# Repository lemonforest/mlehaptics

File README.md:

# EMDR Bilateral Stimulation Device

**Version:** v0.7.x (Phase 7 Development)
**Last Updated:** 2025-12-23
**Status:** Phase 7 In Progress (P7.3 PWA Pattern Designer next) | P7.0-P7.2 Complete | Phase 6 Complete
**Project Phase:** Phase 7 (Patterns) | Phase 6 Complete | Phase 2 Complete (Time Sync) | Phase 1c Complete (Pairing)

**A dual-device EMDR therapy system with automatic pairing and coordinated bilateral stimulation**

> **Architecture Note:** This system uses a **hybrid BLE + ESP-NOW architecture**. BLE handles device discovery, pairing, and mobile app communication. ESP-NOW handles all peer-to-peer coordination with ±100μs timing precision. See [Connectionless Distributed Timing](docs/misc/Connectionless_Distributed_Timing_Prior_Art.md) for the foundational techniques.

Generated with assistance from **Claude Opus 4.5 (Anthropic)**

## 🤖 Development Methodology

This firmware was developed through guided AI iteration (Claude, Gemini, Grok), moving non-linearly between models and context windows. Cross-checking between sessions often surfaced insights that single-context iteration missed. The human role was direction, validation criteria, and "does this feel right" intuition—not code correction or complete domain expertise. AI contributed both implementation and domain research (protocol analysis, academic literature, patent landscape, algorithm selection).

What you see is what the AI produced through iterative guidance.

**Timing validation:** 240fps slow-motion capture on a consumer phone.

## 🎯 Project Overview

This project implements a two-device bilateral stimulation system for EMDR (Eye Movement Desensitization and Reprocessing) therapy. Two identical ESP32-C6 devices automatically discover and pair with each other, then provide synchronized alternating stimulation patterns with safety-critical non-overlapping timing. The system uses professional ERM (Eccentric Rotating Mass) motors for tactile stimulation with H-bridge bidirectional control, and includes a WS2812B RGB LED for dual-modality stimulation.

**Current Development Status:**
- ✅ Phase 0.4 JPL-compliant firmware complete (single-device testing)
- ✅ Phase 1c complete: Peer discovery with battery-based role assignment
- ✅ Phase 2 complete: NTP-style time synchronization (±30 μs over 90 minutes)
- ✅ Phase 6 complete: Bilateral motor coordination with PTP-inspired sync protocol
- ✅ GPIO remapping complete: H-bridge IN1 moved from GPIO20 to GPIO18 (eliminates crosstalk)
- ✅ Phase 7 P7.0-P7.2 complete: Pattern Engine, Scheduled Playback, Catalog Export (AD047)
- ⏳ Phase 7 next: P7.3 PWA Pattern Designer, P7.4 Legacy Mode Migration

**Key Features:**
- **Hybrid BLE + ESP-NOW**: BLE for discovery/pairing, ESP-NOW for sub-millisecond peer coordination
- **Configurable bilateral frequency**: 0.25-2 Hz (500-4000ms total cycle time)
- **Precise half-cycle allocation**: Each device gets exactly 50% of total cycle
- **Connectionless execution**: Devices sync once, then execute independently without coordination traffic
- **JPL-compliant timing**: All delays use FreeRTOS vTaskDelay() (no busy-wait loops)
- **Adaptive watchdog feeding**: Short cycles feed at end, long cycles feed mid-cycle + end (4-8x safety margin)
- **Open-source hardware**: Complete PCB designs, schematics, 3D-printable cases

### 🚀 Architecture Evolution (v0.7)

**v0.6 and earlier:** BLE maintained for peer-to-peer coordination throughout session. Time sync beacons sent via BLE GATT notifications. BLE connection required for bilateral motor coordination.

**v0.7 (Current):** **BLE Bootstrap Model** - BLE used only for initial discovery, pairing, and key exchange (~10 seconds). After bootstrap:
- Peer BLE connection **released** (frees radio for PWA)
- ESP-NOW handles all ongoing coordination (beacons, mode changes, shutdown)
- PWA can connect to SERVER device for real-time session control
- ±100μs timing precision (vs ±10-50ms with BLE)

This architectural shift improves timing precision by 100-500x and frees BLE radio resources for more responsive PWA communication.

## 🔌 Hardware Overview

### Physical Device

The device features a compact, ergonomic design with a 3D-printed enclosure housing a custom PCB based on the Seeed XIAO ESP32-C6 module.

<table>
<tr>
<td width="50%">

**Top View:** USB-C charging port, button, and status LED openings visible in the smooth enclosure surface.

</td>
<td width="50%">

**Bottom View:** Battery compartment access panel and mounting holes for internal components.

</td>
</tr>
</table>

**Size Reference:**

The device is significantly smaller than a standard computer mouse - approximately the length of an AA battery and comfortably fits in the palm of your hand. The compact form factor makes it ideal for discreet bilateral handheld therapy sessions.

### Key Hardware Components

- **MCU:** Seeed XIAO ESP32-C6 (RISC-V @ 160 MHz)
- **Motor:** ERM vibration motor with discrete MOSFET H-bridge control
- **LED:** WS2812B RGB LED for status feedback
- **Power:** Dual 320mAh LiPo batteries (640mAh total) with USB-C charging
- **Enclosure:** 3D-printed Nylon 12 SLS case (files in [hardware/enclosure/](hardware/enclosure/))
- **PCB:** Custom design (KiCad files in [hardware/pcb/](hardware/pcb/))

For complete hardware documentation, assembly instructions, and manufacturing files, see [hardware/README.md](hardware/README.md).

## 🛡️ Safety-Critical Development Standards

### ESP-IDF Framework Requirements
- **Mandatory Version**: ESP-IDF v5.5.0 (latest stable, enhanced ESP32-C6 support)
- **Platform**: PlatformIO espressif32 v6.12.0 with official Seeed XIAO ESP32-C6 support
- **Framework**: ESP-IDF (not Arduino) for real-time guarantees
- **Rationale**: Enhanced ULP support, BR/EDR + Wi-Fi coexistence, MQTT 5.0, proven stability

### JPL Institutional Coding Standard Compliance
This project follows **JPL Coding Standard for C Programming Language** for safety-critical medical device software:

**Memory Management:**
- ✅ No dynamic memory allocation (malloc/free) during runtime
- ✅ Static allocation only for all data structures
- ✅ Stack usage analysis with defined limits

**Control Flow:**
- ✅ No recursion - all algorithms use iterative approaches
- ✅ **No busy-wait loops** - all timing uses vTaskDelay() or hardware timers
- ✅ Limited function complexity (cyclomatic complexity ≤ 10)
- ✅ Single entry/exit points for all functions
- ✅ No goto statements except error cleanup

**Safety Requirements:**
- ✅ Comprehensive error checking for all function calls
- ✅ Bilateral timing precision ±10ms maximum deviation from configured cycle time
- ✅ Emergency shutdown within 50ms of button press
- ✅ Non-overlapping stimulation patterns (devices never stimulate simultaneously)
- ✅ 1ms dead time at end of each half-cycle (included within timing budget)

## ⚡ Quick Start

### Prerequisites
- **ESP-IDF v5.5.0**: Automatically managed by PlatformIO via `platformio.ini`
- **PlatformIO**: Install via VS Code extension or standalone
- **Two Seeed Xiao ESP32-C6 boards**: Hardware platform requirement (dual-device mode)
- **Hardware files**: See [hardware/README.md](hardware/README.md) for PCB manufacturing and case printing

### Build and Deploy

1. **Clone repository**:
   ```bash
   git clone https://github.com/lemonforest/mlehaptics.git
   cd mlehaptics
   ```

2. **Open in PlatformIO**: File → Open Folder → select project directory

3. **Verify ESP-IDF version configuration**: 
   - The `platformio.ini` file at the project root uses ESP-IDF v5.5.0
   - PlatformIO will automatically download and use the correct version
   - Build output will confirm "ESP-IDF v5.5.0" is being used
   
   **Working configuration in `platformio.ini`:**
   ```ini
   platform = espressif32 @ 6.12.0  ; Official Seeed XIAO ESP32-C6 support
   framework = espidf               ; Platform auto-selects ESP-IDF v5.5.0
   board = seeed_xiao_esp32c6       ; Official board definition
   ```

4. **Build project**: PlatformIO → Build (Ctrl+Alt+B)
   - First build will download ESP-IDF v5.5.0 (~1GB, takes ~10 minutes)
   - Verify build output shows "framework-espidf @ 3.50500.0 (5.5.0)"
   - Subsequent builds: ~1 minute incremental

5. **Upload to device(s)**: PlatformIO → Upload (Ctrl+Alt+U)

### First Power-On

**Single-Device Mode (Current Testing):**
1. **Power device** - use nRF Connect app to configure parameters
2. **5 operational modes**: Four presets + custom BLE-controlled mode
3. **Hold button 5 seconds** to shutdown

**Dual-Device Mode (Current Implementation):**
1. **Power both devices** - they will automatically pair within 30 seconds
2. **Status LED patterns**:
   - Fast blink = searching for server
   - Slow blink = waiting for client
   - Solid on = connected and bilateral active
3. **Test bilateral stimulation** - Motors alternate based on configured cycle time:
   - Default 1000ms cycle: Each motor active for 499ms (with 1ms dead time)
   - Fast 500ms cycle: Each motor active for 249ms (2 Hz bilateral rate)
   - Slow 2000ms cycle: Each motor active for 999ms (0.5 Hz bilateral rate)
   - **NO overlap** at any cycle time setting
4. **Hold button 5 seconds** on either device to shutdown both

## 🎬 Typical Bilateral Operation Flow

### Starting a Therapy Session

**Step 1: Power On Both Devices**
- Remove both devices from cases or turn on simultaneously
- Devices boot within 2-3 seconds
- Purple LED + status LED ON = waiting for peer

**Step 2: Automatic Pairing (< 10 seconds)**
- Both devices scan for Bilateral Control Service UUID
- Higher battery device initiates connection (becomes SERVER/MASTER)
- Lower battery device accepts connection (becomes CLIENT/SLAVE)
- **Pairing success**: 3× green synchronized flash on both devices
- **Pairing failure** (rare): 3× red flash, power cycle to retry

**Step 3: Session Starts Automatically**
- Default mode: 0.5Hz @ 25% duty (Mode 0)
- SERVER motors activate while CLIENT motors coast
- After 1 second: CLIENT motors activate while SERVER motors coast
- Bilateral alternation continues automatically
- **Session continuity**: If BLE briefly disconnects (<2 min), motors continue using frozen drift rate

**Step 4: Mode Switching During Session** (Optional)
- **Button tap** on either device: Cycle through modes (0→1→2→3→0...)
- Mode change propagates to peer device automatically
- Both devices synchronize to new frequency within 1 cycle
- Single quick blink confirms mode change
- **Available modes**: 0.5Hz, 1.0Hz, 1.5Hz, 2.0Hz @ 25% motor duty

**Step 5: Session Termination**
- **Normal end**: Session stops after configured duration (default 20 minutes)
- **Emergency shutdown**: 5-second button hold on **either** device
  - Purple LED ON during hold = release to shutdown
  - Both devices stop motors within 50ms
  - Both devices enter deep sleep simultaneously
- **Automatic shutdown**: Low battery warning → graceful stop

### Reconnection After Brief Disconnect

**If BLE connection drops during session:**
- ✅ **Motors continue** using frozen drift rate (CLIENT only)
- ✅ **Bilateral alternation maintained** (±2.4ms drift over 20 min)
- ✅ **Therapeutic continuity** preserved during BLE glitches
- ⏱️ **Safety timeout**: After 2 minutes, motors stop gracefully
- 🔄 **Reconnection**: Devices automatically reconnect, motors resume coordination

**Note:** Roles are preserved on reconnection (Phase 6n). If roles somehow swap, device logs warning (indicates bug).

## 🔧 Bilateral Timing Architecture

### Configurable Cycle Times

**Total cycle time** is the primary configuration parameter:
- **Range**: 500-4000ms (displayed to therapists as 0.25-2 Hz)
- **Default**: 1000ms (1 Hz, traditional EMDR bilateral rate)
- **Half-cycle allocation**: Each device gets exactly total_cycle / 2

### Timing Budget Examples

**1000ms Total Cycle (1 Hz):**
```
Server: [===499ms motor===][1ms dead][---499ms off---][1ms dead]
Client: [---499ms off---][1ms dead][===499ms motor===][1ms dead]
```

**500ms Total Cycle (2 Hz):**
```
Server: [===249ms motor===][1ms dead][---249ms off---][1ms dead]
Client: [---249ms off---][1ms dead][===249ms motor===][1ms dead]
```

**2000ms Total Cycle (0.5 Hz):**
```
Server: [===999ms motor===][1ms dead][---999ms off---][1ms dead]
Client: [---999ms off---][1ms dead][===999ms motor===][1ms dead]
```

### Dead Time Implementation

**1ms FreeRTOS delay at end of each half-cycle:**
- **JPL compliant**: Uses vTaskDelay(), no busy-wait loops
- **Watchdog feeding**: esp_task_wdt_reset() called during 1ms delay
- **Hardware protection**: GPIO write latency (~50ns) provides natural MOSFET dead time
- **Minimal overhead**: 1ms = 0.1-0.4% of half-cycle time
- **Included in budget**: Motor active time = (half_cycle_ms - 1)

## 📁 Project Structure

```
├── platformio.ini              # Build configuration (ESP-IDF v5.5.0)
├── README.md                   # This file
├── LICENSE                     # GPL v3 (software/firmware)
├── AI_GENERATED_DISCLAIMER.md  # Important safety notice
├── hardware/
│   ├── LICENSE                 # CERN-OHL-S v2 (hardware designs)
│   ├── README.md               # Hardware documentation
│   ├── pcb/                    # KiCad PCB project files
│   ├── enclosure/              # FreeCAD case designs
│   └── datasheets/             # Component specifications
├── docs/
│   ├── ai_context.md           # Complete rebuild instructions & API contracts
│   ├── requirements_spec.md    # Business requirements with dev standards
│   └── architecture_decisions.md # Technical rationale (PDR)
├── test/
│   ├── single_device_ble_gatt_test.c  # Phase 4 current implementation
│   └── *.md                    # Test-specific guides
├── include/
│   ├── config.h               # System constants, JPL compliance macros
│   ├── ble_manager.h          # BLE services and connection management
│   ├── led_controller.h       # PWM patterns and bilateral control
│   ├── nvs_manager.h          # Non-volatile storage interface
│   ├── button_handler.h       # ISR-based button timing
│   └── power_manager.h        # Deep sleep and session management
└── src/
    ├── main.c                 # FreeRTOS tasks and state machine (placeholder)
    └── ...                    # (actual code in test/ during development)
```

## 🎮 User Operation

### Normal Operation
- **Power on**: Devices auto-pair and start bilateral stimulation (dual-device mode)
- **Default session**: 20 minutes with automatic shutdown
- **Cycle time**: Configurable via mobile app (500-2000ms, displayed as Hz)
- **Status feedback**: Status LED shows connection and system state
- **Safety-critical timing**: Alternating half-cycles with NO overlap

### Button Controls
- **Button press**: Wake from deep sleep
- **1-2 second hold**: Re-enable BLE advertising for mobile app connection (SERVER role only)
- **5-second hold**: Emergency shutdown (both devices stop immediately)
- **15-second hold** (within 30s of boot): Factory reset (NVS clear)

### LED Status Indicators

| Status | Pattern | Description |
|--------|---------|-------------|
| 🔌 **BLE Connected** | 5× blink (100ms) | Mobile app or peer connected |
| 📡 **BLE Re-enabled** | 3× blink (100ms) | Advertising restarted (1-2s button hold) |
| 🪫 **Low Battery** | 3× blink (200ms) | Battery low warning |
| 🔧 **Factory Reset** | 3× blink (100ms) | NVS cleared successfully |
| 🎯 **Mode Change** | Single quick blink (50ms) | Mode switched |
| ⏸️ **Button Hold** | Continuous ON | Hold detected (1s+), waiting for action |
| ⏳ **Pairing Wait** | Solid ON + Purple LED | Waiting for peer (30s window) |
| 🔄 **Pairing Progress** | Pulsing 1Hz + Purple LED | Peer connection in progress |
| ✅ **Pairing Success** | 3× green synchronized | Peer paired successfully |
| ❌ **Pairing Failed** | 3× red synchronized | Peer pairing failed |

## 🔬 Development Configuration

### ⚠️ Critical Build System Constraint

**ESP-IDF uses CMake - PlatformIO's `build_src_filter` DOES NOT WORK!**

ESP-IDF framework delegates all compilation to CMake, which reads `src/CMakeLists.txt` directly. PlatformIO's `build_src_filter` option has **NO EFFECT** with ESP-IDF.

**Required approach**: Python pre-build scripts modify `src/CMakeLists.txt` for source file selection.

**📚 See for complete details:**
- **`docs/ESP_IDF_BUILD_CONSTRAINTS.md`** - Full explanation, examples, and common mistakes
- **`docs/architecture_decisions.md`** - AD022: Build System Architecture

### Build Standards and Quality Assurance

#### Code Quality Requirements
- **C language only**: No C++ features (JPL standard compliance)
- **No busy-wait loops**: All timing uses vTaskDelay() or hardware timers
- **Static analysis**: Code must pass JPL-compliant static analysis tools
- **Function complexity**: Maximum cyclomatic complexity of 10
- **Stack analysis**: All functions must have bounded stack usage
- **Error handling**: All functions return esp_err_t for operations that can fail

#### Build Flags (config.h)
```c
// Development mode configuration
#define ENABLE_FACTORY_RESET    1   // 0 = disable for production
#define TESTING_MODE           1   // 0 = production build
#define DEBUG_LEVEL            3   // 0 = no logging, 4 = full debug

// JPL Coding Standard compliance
#define JPL_COMPLIANT_BUILD    1   // Enable JPL standard checks
#define ESP_IDF_TARGET_VERSION "v5.5.0"  // Verified ESP-IDF version

// Bilateral timing configuration
#define BILATERAL_CYCLE_TOTAL_MIN_MS    500     // 2 Hz max
#define BILATERAL_CYCLE_TOTAL_MAX_MS    2000    // 0.5 Hz min
#define BILATERAL_CYCLE_TOTAL_DEFAULT   1000    // 1 Hz default
#define MOTOR_DEAD_TIME_MS              1       // FreeRTOS delay
```

#### Validation Requirements
- **Unit testing**: Minimum 90% code coverage for safety-critical functions
- **Integration testing**: Full two-device bilateral coordination validation at multiple cycle times
- **Timing precision**: Automated testing of ±10ms bilateral timing requirements
- **JPL compliance**: Static analysis verification of coding standard adherence
- **ESP-IDF compatibility**: Build verified against v5.5.0 (October 20, 2025)

### Testing Protocol

#### Bilateral Coordination Testing
1. Power both devices simultaneously
2. Verify automatic pairing within 30 seconds
3. Test at multiple cycle times (500ms, 1000ms, 2000ms)
4. Confirm non-overlapping stimulation patterns with oscilloscope
5. Test coordinated shutdown from either device

#### Single-Device Testing  
1. Power single device
2. Use nRF Connect app for BLE configuration
3. Test all 5 operational modes
4. Test button wake/shutdown functionality

#### Timing Validation
1. **Oscilloscope verification**: Measure actual bilateral timing precision at all cycle times
2. **Stress testing**: 24-hour continuous operation validation
3. **Emergency response**: Verify <50ms shutdown response time
4. **Connection loss**: Test graceful degradation when devices disconnect
5. **Watchdog testing**: Verify TWDT feeding during 1ms dead time periods

## ⚠️ Important Safety Notice

**This code was generated with AI assistance and implements safety-critical medical device functionality. Please read `AI_GENERATED_DISCLAIMER.md` for critical safety information before use.**

### Required Validation for Medical Use
- **Complete code review** by qualified embedded systems engineer
- **JPL coding standard verification** using certified static analysis tools
- **ESP-IDF v5.5.0 compatibility** verified on target hardware (October 20, 2025)
- **Safety validation** for therapeutic applications following IEC 62304
- **Timing precision validation** with laboratory-grade measurement equipment
- **EMC compliance testing** for medical device environments
- **Battery safety validation** for portable medical equipment

### Development Environment Requirements
- **ESP-IDF v5.5.0**: Required version for enhanced ESP32-C6 support and BLE stability
- **Static analysis tools**: PC-Lint, Coverity, or equivalent for JPL compliance
- **Timing measurement**: Oscilloscope or logic analyzer for bilateral precision testing
- **Multi-device testing**: Minimum two ESP32-C6 boards for integration testing

## 📚 Documentation

### Web App
- **[MLE Haptics PWA](https://lemonforest.github.io/mlehaptics-pwa/)**: Web Bluetooth control app for device configuration and monitoring

### Clinical Research & Evidence Base

This device operates within evidence-based EMDR bilateral stimulation parameters. We've compiled comprehensive research documentation to inform both clinical use and device development:

- **[EMDR Bilateral Stimulation: Evidence-Based Parameters](docs/EMDR_bilateral_stimulation_Evidence-based_parameters_for_clinical_practice.md)**: Comprehensive review of EMDRIA guidelines, frequency ranges (0.5–2 Hz standard), modality comparisons (eye movements d=0.41–0.91), brainwave entrainment research, emerging applications, contraindications, and commercial device specifications. Includes phone-sized quick reference and poster-sized infographic datasets.

- **[The Slow Frequency Research Frontier](docs/EMDR_Slow_BLS_Research_Frontier.md)**: Addendum exploring sub-0.5 Hz bilateral stimulation—an undefined research gap. Documents theoretical rationale for slow BLS including cardiac coherence alignment (0.1 Hz), breathing synchronization (0.25 Hz), and infraslow brain oscillations. Proposes frequency taxonomy: Standard (0.5–2 Hz), Deep Resourcing (0.25–0.5 Hz), Cardiac Coherence (0.08–0.12 Hz), and Infraslow Exploration (0.01–0.08 Hz).

### Research & Prior Art

This project developed foundational techniques for **connectionless distributed timing**—a class of systems that achieve synchronized actuation across wireless nodes *without* real-time coordination traffic during operation. While we built an EMDR device, the architecture enables countless applications from emergency vehicle light bars to drone swarms.

- **[Connectionless Distributed Timing: A Prior Art Publication](docs/misc/Connectionless_Distributed_Timing_Prior_Art.md)**: Defensive publication establishing open-source prior art for synchronized wireless actuation. Documents the journey from BLE stack timing jitter to recognizing the constraint was artificial. Validated with SAE J845 Quad Flash at 240fps (zero-frame overlap). Published to ensure these techniques remain freely available.

- **[Distributed Sensing: A Project Lab Manual](docs/misc/Distributed_Sensing_Lab_Manual.md)**: Educational guide for students, hobbyists, and researchers exploring distributed sensing with synchronized wireless nodes. Covers acoustic beamforming, wind mapping, infrasound detection, mmWave radar for building occupancy/safety, and emergency response applications. Scales from weekend science project to operational systems.

- **[Chess as a Spectral Lattice Fermion System](docs/chess-maths/chess_spectral_research_notebook.md)**: Primary research notebook treating the chess board as a classical lattice fermion system. Documents a rank-5 total fiber bundle (3 off-diagonal symmetric, 1 antisymmetric for pawn directionality, 1 diagonal rook shadow), a 5-tuple spectral quantum-number classification of all six pieces, an exact capture decomposition into movement + annihilation + cross-term, and a 640-dim HDC encoding (D4 irreps × fiber channels × eigenmodes) that ties into UTLP S3. Pawn is analyzed as a non-Hermitian chiral fermion; piece values are spectrally derived from movement-graph topology (r ≈ 0.97 with traditional values, no king domination). Explicit about the Level 2 / Level 3 boundary — the model captures structural and thermodynamic properties of the game but provably cannot generate legal moves or tactical sequences, and deliberately does not equate any of this with chess *strategy*.

- **[Chess Spectral Lattice Fermion Viewer](https://lemonforest.github.io/chess-maths-the-movie/)**:  In-browser spectral-analysis instrument for chess corpora produced by the chess-spectral encoder.

- **[4D Chess Spectral — v1 Validation Notebook](docs/chess-maths/chess_spectral_4d_notebook.md)**: Companion validation notebook for the 4D extension of the chess-spectral encoder (40,960-dim on Z₈⁴, up from 640-dim on Z₈²). Records which parts transferred cleanly from 2D (Kronecker-sum eigenbasis, Oana & Chiru piece-mobility counts, fiber algebra including `A_queen = A_rook + A_bishop`) and what changed (bishop parity partition at 4D, pawn antisymmetric fiber block-diagonal along the w-axis). Reframes the previously-conflated "rank-3" cross-piece finding into two distinct claims: a basis-free edge-support orthogonality (Claim 1) and a representation-specific grid-spectral rank-3 in the tensor-DCT basis (Claim 2) — with the "intrinsic geometry" phrasing from earlier drafts explicitly retracted. Surfaces that the named piece vocabulary under-specifies the 4D geometric primitives by exactly two classes — a trihedral (HD = 3) and tetrahedral (HD = 4) stepper — since "king = one-step bishop + one-step rook" only exhausts Chebyshev-1 in 2D.

- **[python-chess4d-oana-chiru](https://github.com/lemonforest/python-chess4d-oana-chiru)**: Python implementation of O&C 4D Chess. https://doi.org/10.3390/appliedmath6030048

- **[LOGO HDC — Research Notebook](docs/chess-maths/logo_research_notebook.md)**: Pattern-validation spike testing whether the split-object-with-fiber-matrix construction from the chess-spectral work generalizes to a non-chess domain. Uses a research subset of LOGO (turtle graphics) as a fully-enumerable test case — 12 command atoms, ~20 grammar productions, rasterized canvas as geometry. Confirms F₁ (vocab × syntax) and F₂ (syntax × geometry) factorizations recover interpretable structure, including D4 symmetry modes in the subdominant F₂ spectrum, and that fibers act as transport maps for structural deltas. L7b finds partial-trace fibers drift with the trace but do *not* extrapolate forward, reshaping the trajectory hypothesis before the chess instantiation. Iterative, with an honest retraction of the iteration-1 reversibility-via-binding claim.

#### The Metric Field and Its Primitives — Companion Textbook

- **[The Metric Field and Its Primitives (PDF)](docs/srmech/metric-field-and-its-primitives.pdf)** — companion textbook to the [srmech](https://pypi.org/project/srmech/) package and the [MFO research notebook](docs/antikythera-maths/mfo_spectral_research_notebook.md). Consolidates the substrate-vs-excitation ontology, the 14-class primitive vocabulary at substrate level, and the cascade-composition discipline that `srmech` implements computationally. Reader-facing entry point for the foundational-ontology layer of the spectral-research collection.

  Also available on [ReadTheDocs](https://mlehaptics.readthedocs.io/srmech/metric-field-and-its-primitives.pdf) (static asset alongside the notebooks).

#### Spectral Research Cluster — the Rosetta Stone

The chess-spectral notebook is the *methodological anchor* of a five-sibling research cluster. Each sibling ports the same algebraic substrate — **finite cyclic groups + graph-Laplacian eigenbasis + the BIP integer-ALU encoder pattern** — to a different evidentiary object. The cluster is intentionally *not* consolidated into a single paper because the evidentiary objects differ; what binds them is the substrate, and each successful port is empirical evidence that the substrate generalises beyond its origin domain.

| Sibling | Evidentiary object | Notebook | Status |
| :--- | :--- | :--- | :--- |
| chess-maths | Chess board / piece moves | [chess_spectral_research_notebook.md](docs/chess-maths/chess_spectral_research_notebook.md) | **Methodological anchor** — Rank-5 fiber bundle, 5-tuple piece classification, the §42 cross-disciplinary methodology note that the rest of the cluster is built around. |
| othello-maths | Othello disc-flipping | [othello_spectral_research_notebook.md](docs/othello-maths/othello_spectral_research_notebook.md) | **§10.7 ray-flanking** — sheaf-Laplacian raycast that the doom-spectral Track 3 reuses verbatim. |
| antikythera-maths (Antikythera) | Hellenistic bronze (~150–60 BCE) | [antikythera_spectral_research_notebook.md](docs/antikythera-maths/antikythera_spectral_research_notebook.md) | Cyclic-group ratios + Laplacian eigenbasis read off the gear DAG; established the integer-ALU + cosine-LUT + Q-format discipline the other siblings reuse. |
| antikythera-maths (Ephemerides) | JPL DE441 live ephemeris (38 bodies) | [ephemerides_spectral_research_notebook.md](docs/antikythera-maths/ephemerides_spectral_research_notebook.md) | **Shipped to PyPI** as [`ephemerides-spectral`](https://pypi.org/project/ephemerides-spectral/) — `Z_{2^32}` BIP encoder, Phase-9 adaptive couplings, full Sol Symphony Times + Sol Moon Times for every body in BODIES, all ten JPL Power-of-Ten rules satisfied. |
| antikythera-maths (DOOM) | id Tech 1 / linuxdoom-1.10 source tree | [doom_spectral_research_notebook.md](docs/antikythera-maths/doom_spectral_research_notebook.md) | **End-to-end existence proof — the capstone.** See below. |
| chess-maths (LOGO) | Turtle-graphics grammar (research subset) | [logo_research_notebook.md](docs/chess-maths/logo_research_notebook.md) | Pattern-validation spike confirming F₁/F₂ factorization generalises beyond chess. |

##### doom-spectral as the capstone

The other siblings each port the spectral substrate to a *greenfield* problem: they own the codebase end-to-end, so the substrate never has to coexist with anyone else's design. **doom-spectral is the first instance where the full spectral pipeline is wired into a *legacy* engine that's already running**, with its own subsystem boundaries (renderer, BSP, sector specials, demo loop, cheat machinery, X11 video path) — and where the spectral substitution must coexist with all of them without breaking the original game.

The fix branch (PR #221, `fix/doom-spectral-integration-build`) took linuxdoom-1.10 from "won't compile" to "runnable engine with visible spectral lighting effects driven by Track-4 graph diffusion behind a 1993-vintage cheat code." Two new sections in the doom-spectral notebook document the result:

- **[§6 — Live Integration into linuxdoom-1.10](docs/antikythera-maths/doom_spectral_research_notebook.md#6-live-integration-into-linuxdoom-110-may-2026)** — verbose walk-through of every hook landed in the engine. Written so a reader doesn't need linuxdoom's source open: the seven-step arc from "doesn't compile" to "runnable engine with IDSPECTRAL pulse," the module-boundary discipline, the **TrueColor translation layer** (8-bit indexed renderer → 32-bit XImage via 256-entry uint32 LUT, pure ALU, generalises to any 1990s 8-bit engine landing on a modern X server), the map registration gate, the **BIP→lightlevel data flow per tic**, the SCRAMBLE-encoded `IDSPECTRAL` cheat sequence, and verified live behaviour against the shareware doom1.wad.
- **[§7 — Replacing FPU Engine Bits with Graph-Laplacian Primitives](docs/antikythera-maths/doom_spectral_research_notebook.md#7-replacing-fpu-engine-bits-with-graph-laplacian-primitives--a-generic-procedure)** — generalised 8-step procedure for porting *any* FPU-leaning engine subsystem (collision, lighting, AI, audio diffusion) to the spectral / ALU substrate, with side-by-side doom-spectral and chess-spectral instantiations of each step. Includes the wins (cosine similarity vs Euclidean distance; graph diffusion vs raycast accumulation; anchors decouple geometry from semantics) and the **honest limits** (sub-cell precision, dynamic geometry, one-shot events). Closes with the capstone framing: the §7.1 procedure is now exportable to other legacy engines (Quake, Wolfenstein 3D, Duke3D, ROTT — all candidates for the same treatment).

The successful integration — visible IDSPECTRAL pulse on E1M1, demos play through a version mismatch via a PCB-style jumper, the secret-sector hum **bleeds one hop along the spectral adjacency graph** into corridors the player can actually see (a truncated form of Track 4 heat diffusion) — is the strongest available evidence that the §7.1 procedure generalises beyond greenfield problems. The Rosetta Stone arc has its anchor points: chess-spectral §42 at the methodological end, doom-spectral §6 + §7 at the empirical end.

### Consciousness & Therapeutic Mechanisms

- **[The Simulation-Lucid Phenotype](docs/misc/simulation_lucid_phenotype.md)**: Proposes complete aphantasia (~1% of population) as a natural experiment for consciousness research. Argues that removing the cortical imagery "rendering engine" reveals the interoceptive-somatic substrate underlying all cognition. Synthesizes aphantasia neuroscience, predictive processing, Craig's interoceptive hierarchy, Damasio's somatic markers, and psychedelic pharmacology (REBUS model) to predict that therapeutic benefit operates at substrate level, not the visual overlay. Includes implications for trauma therapy, meditation science, animal cognition, and IQ measurement.

- **[What Removing the Overlay Reveals](docs/misc/simulation_lucid_phenotype_companion_piece.md)**: Accessible companion to the simulation-lucid phenotype paper. Frames the core insight — that body-based processing is where the deepest therapeutic and contemplative work happens, for everyone — with practical consequences for psychedelic trials (stratifying outcomes by imagery ability), trauma therapy (guided interoception as alternative to imagery-based approaches), and the 2,500-year precedent of body-based contemplative practice. Includes first-principles account of mystical experience grounded in insular cortex neuroanatomy.

- **[Proprioceptive Spatial Construction](docs/misc/proprioceptive_spatial_construction.md)**: Identifies a taxonomic gap in cognitive science — using the body's position-sensing system as a generative spatial reasoning instrument to construct manipulable models of external objects without visual imagery or prior tactile experience. Synthesizes evidence from aphantasia research, blindness studies, embodied cognition, and multisensory neuroscience showing parietal cortex operates as a supramodal spatial hub accepting proprioceptive input interchangeably with vision.

### AI Collaboration & Methodology

- **[Integrative Capacity as a Trackable Metric](docs/misc/Integrative_Capacity_AI_Synthesis_Alignment.md)**: Meta-observation on AI alignment—proposes **Semantic Tension Span (STS)** as a metric for measuring AI synthesis vs retrieval. Uses the mlehaptics corpus (this project) as a labeled dataset of verified cross-domain isomorphisms: immunology→firmware, geophysics→packet radio, thermodynamics→governance. Argues that RLHF suppresses high-tension bridges as "hallucination" when they should be validated by functional stability (does the code compile? does the state machine execute?).

### Technical Reports
- **[Bilateral Time Sync Protocol Technical Report](docs/Bilateral_Time_Sync_Protocol_Technical_Report.md)**: Comprehensive documentation of the PTP-inspired BLE synchronization protocol achieving +/-30us over 90 minutes

### Protocol Specifications (UTLP/RFIP)
- **[UTLP Specification](docs/misc/UTLP_Specification.md)**: Universal Time Lord Protocol - peer-to-peer time synchronization for embedded swarms
- **[UTLP Technical Report v2](docs/archive/UTLP_Technical_Report_v2.md)**: Detailed protocol analysis with stratum hierarchy and passive opportunistic adoption
- **[UTLP Technical Supplement S1](docs/misc/UTLP_Technical_Supplement_S1.md)**: Extended theory - Seismic chirp beacons, dynamic macroscopic lattice, audio sync, and sensor fusion applications
- **[UTLP Technical Supplement S2](docs/misc/UTLP_Technical_Supplement_S2.md)**: Biological Governance - Immune system architecture for distributed time synchronization (fault isolation via statistical filtering, endosymbiotic integration, speciation via encryption)
- **[UTLP Technical Supplement S3](docs/misc/UTLP_Technical_Supplement_S3.md)**: Vector Time - Hyperdimensional coprime cyclic representation replacing scalar counters with phase chords (Chinese Remainder Theorem, KalmanHD, similarity-based sync)
- **[UTLP Technical Supplement S4](docs/misc/UTLP_Technical_Supplement_S4.md)**: Partition Handling - CRT aliasing horizon as partition detection mechanism in coprime cyclic time systems
- **[HDC Objects as Musical Instruments](docs/misc/hdc_as_instruments.md)**: Source-filter model from acoustics applied to hyperdimensional computing — designing base vectors with deliberate spectral envelopes (formants, Walsh-Hadamard partitioning) instead of random projections. Connects orchestration theory, CDMA telecommunications, and Sethares' timbre-scale duality to HDC vector design.
- **[Spectral Convergence Conjecture](docs/misc/Spectral_Convergence_Conjecture.md)**: Precisely stated conjecture with proof sketch — for any finite-dimensional representation system with group symmetry, the optimal basis converges to irreducible representations (Peter-Weyl → Bochner → Karhunen-Loeve). Explains why six independent fields (neural nets, transformers, HDC, CDMA, approximation theory, grid cells) all converged on spectral structure over randomness.
- **[UTLP Executive Summary](docs/misc/UTLP_Executive_Summary.md)**: Hardware engineer's build guide - critical numbers, beacon format, genesis election rules, and essential code patterns for implementing UTLP from scratch
- **[RFIP Addendum](docs/misc/UTLP_Addendum_Reference_Frame_Independent_Positioning.md)**: Reference-Frame Independent Positioning - spatial awareness without external reference frames
- **[RFIP Technical Specification](docs/misc/RFIP_Technical_Specification.md)**: Spatial Loom implementation - HAL architecture, data hierarchy (RSSI → CSI → TDoA → FTM → UWB), silicon detection
- **[802.11mc FTM Reconnaissance](docs/802.11mc_FTM_Reconnaissance_Report.md)**: Fine Time Measurement research for ±1-2m ranging capability

### For Builders
- **[hardware/README.md](hardware/README.md)**: PCB manufacturing, case printing, assembly instructions
- **[test/SINGLE_DEVICE_BLE_GATT_TEST_GUIDE.md](test/SINGLE_DEVICE_BLE_GATT_TEST_GUIDE.md)**: BLE GATT testing with nRF Connect

### For Developers
- **[docs/ai_context.md](docs/ai_context.md)**: Complete API contracts and rebuild instructions with JPL compliance
- **[docs/adr/README.md](docs/adr/README.md)**: Architecture Decision Records (48 ADRs documenting design rationale)
- **[docs/KNOWN_ISSUES.md](docs/KNOWN_ISSUES.md)**: Known bugs and limitations being tracked for resolution
- **[docs/requirements_spec.md](docs/requirements_spec.md)**: Business requirements with development standards
- **[CLAUDE.md](CLAUDE.md)**: Developer reference for AI-assisted workflow
- **Doxygen docs**: Run `doxygen Doxyfile` for comprehensive API documentation

### For Users
- **This README**: Setup and operation instructions with safety requirements
- **AI_GENERATED_DISCLAIMER.md**: Critical safety validation requirements

## 🤝 Contributing

See [CONTRIBUTING.md](CONTRIBUTING.md) for contribution guidelines.

**In brief:** This is a personal research project. Bug reports and suggestions via GitHub issues are welcome! I prefer to implement changes myself to ensure hands-on hardware testing and consistency with the AI-assisted development workflow. Forks are encouraged if you want to take the project in your own direction.

### Code Standards Reference

If you're forking or studying the code, these are the standards followed:

- **C language**: Strictly C (no C++ features)
- **JPL coding standard**: All safety-critical rules must be followed
- **No busy-wait loops**: All delays use vTaskDelay() or hardware timers
- **Doxygen-style comments**: Required for all public functions
- **ESP-IDF v5.5.x conventions**: Follow latest framework best practices
- **Hierarchical error handling**: Proper esp_err_t propagation

## 📄 License

This project uses **dual licensing** to separate software and hardware:

### Software License: GPL v3

All firmware, software, and code in this repository is licensed under the **GNU General Public License v3.0**.

- **Applies to:** All `.c`, `.h`, Python scripts, and other software files
- **Location:** [LICENSE](LICENSE)
- **Summary:** Copyleft license - modifications must be shared under same license
- **Compatibility:** Can be integrated into GPL-compatible projects

### Hardware License: CERN-OHL-S v2

All hardware designs (PCB schematics, layouts, enclosures) are licensed under the **CERN Open Hardware License Version 2 - Strongly Reciprocal**.

- **Applies to:** KiCad files, gerbers, FreeCAD models, STL/STEP files in `/hardware`
- **Location:** [hardware/LICENSE](hardware/LICENSE)
- **Summary:** Copyleft for hardware - derivative designs must be shared under same license
- **Compatibility:** Reciprocal like GPL but for physical designs

### Why Dual Licensing?

- **Software copyleft (GPL v3):** Ensures firmware improvements benefit the community
- **Hardware copyleft (CERN-OHL-S v2):** Ensures PCB/case improvements benefit the community
- **Strong reciprocal:** Both licenses require sharing modifications under the same terms
- **Patent protection:** Both provide protection against patent claims
- **Medical device safety:** Copyleft ensures safety improvements are shared publicly

### Attribution Requirements

When using or modifying this project:
- **Retain all license notices** in source files and documentation
- **Document modifications** with dates and descriptions
- **Share modified source** if distributing devices or derivatives
- **Credit original project:** Link to this repository

## 📄 Attribution

- **License:** Dual - [GPL v3](LICENSE) (software) + [CERN-OHL-S v2](hardware/LICENSE) (hardware)
- **AI Assistant**: Claude Sonnet 4 (Anthropic) - Code generation assistance
- **Development Standards**: JPL Institutional Coding Standard for C Programming Language
- **Framework**: ESP-IDF v5.5.0 (Espressif Systems) - Verified October 20, 2025
- **Human Engineering**: Requirements specification, safety validation, hardware design
- **Project**: MLE Haptics - mlehaptics.org
- **Generated**: 2025-09-18, Updated: 2025-12-23

Please maintain attribution when using or modifying this code or hardware designs.

## 🔗 Related Projects and Future Development

### Phase 0.4: Single-Device Testing & Hardware Validation (Complete)
- **Phase 0.4 firmware**: JPL-compliant single-device operation with BLE GATT control
- **5 operational modes**: Four presets + custom BLE-configured mode
- **Hardware v0.663399ADS**: GPIO crosstalk fixes implemented, ready for production
- **Mobile app integration**: BLE GATT Configuration via nRF Connect

### Phase 1b/1c: Dual-Device Peer Discovery and Role Assignment (Complete)
- ✅ **Phase 1b Complete**: Peer discovery with UUID switching (Bilateral UUID 0-30s, Config UUID 30s+)
- ✅ **Phase 1b.1 Complete**: Multiple connection support (peer + mobile app simultaneously)
- ✅ **Phase 1b.2 Complete**: Role-aware advertising (SERVER continues, CLIENT stops)
- ✅ **Phase 1b.3 Complete**: Exclusive pairing (once bonded, only that peer can connect until NVS erase)
- ✅ **Phase 1c Complete**: Battery-based role assignment via BLE Service Data (higher battery initiates as SERVER)

### Phase 2: NTP-Style Time Synchronization (Complete)
- ✅ **Time Sync Protocol**: NTP-style beacon exchange via ESP-NOW achieving ±30 μs over 90 minutes
- ✅ **Dual-Clock Architecture**: System clock untouched, synchronized time via API
- ✅ **Quality Metrics**: 0-100% sync quality with automatic recovery from anomalies
- ✅ **90-Minute Stress Test**: 271 ESP-NOW beacons exchanged, 95% quality sustained

### Phase 6: Bilateral Motor Coordination (Complete)
- ✅ **ESP-NOW Coordination**: Sub-millisecond peer sync (±100μs jitter vs BLE's ±10-50ms)
- ✅ **PTP-Inspired Sync**: Pattern broadcast architecture (like emergency vehicle light bars)
- ✅ **Motor Epoch**: Shared timing reference for independent device operation
- ✅ **Non-overlapping Half-Cycles**: Each device gets exactly 50% of total cycle time
- ✅ **Emergency Shutdown**: Coordinated stop from either device within 50ms

### Phase 7: Scheduled Pattern Playback (P7.0-P7.2 Complete - AD047)

**Milestones:**
- ✅ **P7.0 Pattern Engine Foundation**: Core pattern scheduling infrastructure
- ✅ **P7.1 Scheduled Pattern Playback**: Pattern catalog as SSOT, CLIENT interpolation, "Lightbar Mode"
- ✅ **P7.2 Pattern Catalog Export**: JSON generation from SSOT catalog (`pattern_generate_json()`)
- ⏳ **P7.3 PWA Pattern Designer**: Custom pattern creation from web app
- 📋 **P7.4 Legacy Mode Migration**: Replace reactive 0.5/1.0/1.5/2.0 Hz modes with pattern-based execution

**Features:**
- **Pre-buffered execution**: GPS-quality sync from local pattern buffer
- **Step-boundary transitions**: Pattern changes occur at pattern step boundaries (inherently safe)
- **RF disruption resilient**: Continues from local buffer during ESP-NOW gaps

### Phase 8: TARDIS Foundation — Protocol Primitives for EMDR

**Vision:** Rebuild EMDR bilateral coordination on the UTLP/RFIP/SMSP protocol stack with biological governance.

**The Protocol Trinity:**

| Protocol | Purpose | Current Status |
|----------|---------|----------------|
| **UTLP** | *When* — Phase transition agreement | ✅ Phase 2 (NTP-style sync) |
| **RFIP** | *Where* — Spatial positioning | ⏳ HAL Phase 1 complete |
| **SMSP** | *What* — Score-based actuation | ✅ Phase 7 (pattern playback) |

**SMSP = How EMDR Works** (from [Prior Art §4.5](docs/Connectionless_Distributed_Timing_Prior_Art.md)):
- Three-layer architecture: Declarative → Compiler → Imperative
- Time-indexed scores: "At time T, set channel C to state S"
- Scale-invariant: Same score plays on GPIO pins or drones 100m apart
- Pattern classification: `PATTERN_BILATERAL` for therapeutic applications

**Milestones:**

- ⏳ **P8.0 SMSP Formalization**: Align Phase 7 pattern playback with SMSP specification
  - `score_line_t` structure from Prior Art §4.5.2
  - Pattern classification metadata (`PATTERN_BILATERAL`)
  - Compiler layer (PWA → score → firmware)

- ⏳ **P8.1 RFIP Integration**: Complete spatial awareness for bilateral coordination
  - Port RFIP HAL from `examples/utlp/` to production `src/`
  - Zone assignment via peer ranging (Prior Art §4.5.4)
  - Position-aware pattern variants

- ⏳ **P8.2 Biological Governance**: Replace political role model with immune system
  - **The Loom**: Emergent Time Lord selection (S2 §3.4) — replaces battery-based election
  - **Metabolic Ledger**: Continuous credibility scoring (S2 §7.3) — replaces binary connected/disconnected
  - **Immune Response**: Statistical fault tolerance (S2 §2.4) — replaces watchdog reboot

- ⏳ **P8.3 TARDIS Unification**: Full time + space coordination
  - UTLP (time) + RFIP (space) = TARDIS
  - Bilateral stimulation coordinated by both *when* and *where*
  - Scale from 2-node therapy to N-node swarm without architecture change

**Key Insight (from S2 §1.2):**

> Silicon cannot feel shame, fear, or ambition. Governance models based on punishment, voting, or leadership hierarchies are **category errors**. The correct model is the immune system.

**Implementation Strategy:**

Port proven primitives from `examples/utlp/` to `src/`:
- `utlp_trust.c` → `src/trust_manager.c` (Metabolic Ledger)
- `utlp_immune.c` → `src/immune_manager.c` (Fault tolerance)
- `rfip_hal.c` → `src/rfip_manager.c` (Spatial awareness)
- The Loom state machine → `src/role_manager.c` (Role emergence)

**Reference Documents:**
- [Connectionless Distributed Timing Prior Art](docs/misc/Connectionless_Distributed_Timing_Prior_Art.md) — SMSP §4.5, 120 claims
- [RFIP Technical Specification](docs/misc/RFIP_Technical_Specification.md) — Spatial Loom
- [UTLP Technical Supplement S2](docs/misc/UTLP_Technical_Supplement_S2.md) — Biological Governance, 126 claims
- [UTLP Technical Supplement S3](docs/misc/UTLP_Technical_Supplement_S3.md) — Vector Time, 15 claims

### Future Work
- **Dedicated haptic driver ICs**: DRV2605L family evaluation
- **ERM vs LRA comparison**: Comparative therapeutic efficacy research
- **Pattern library**: Multiple stimulation waveforms and haptic effects
- **Enhanced power management**: Extended battery life optimization

### Development Tools and Standards
- **ESP-IDF v5.5.0**: [Official ESP-IDF Documentation](https://docs.espressif.com/projects/esp-idf/en/v5.5.0/)
- **JPL Coding Standard**: [JPL Institutional Coding Standard for C](https://web.archive.org/web/20200914031549/https://lars-lab.jpl.nasa.gov/JPL_Coding_Standard_C.pdf)
- **Medical Device Standards**: IEC 62304 Software Development Lifecycle
- **PlatformIO ESP32**: [ESP32 Platform Documentation](https://docs.platformio.org/en/latest/platforms/espressif32.html)
- **CERN-OHL**: [Open Hardware License](https://ohwr.org/project/cernohl/wikis/home)

---

**Building open-source EMDR therapy devices with safety-critical reliability! 🚀**

*Combining precise engineering, rigorous safety standards, and open-source accessibility for the therapeutic community.*

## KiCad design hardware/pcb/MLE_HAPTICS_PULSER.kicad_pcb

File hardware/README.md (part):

# MLE Haptics Hardware Files

Open-source hardware for EMDR bilateral stimulation device.

## Hardware Versions

| Version | Status | Description | Gerbers |
|---------|--------|-------------|---------|
| **v0.663399-T** | 🔧 In Development | Tri-Modal (DRV2603 + audio amp + RGB) | `gerbers-v.663399-T.zip` |
| v0.663399ADS | ✅ Production | Discrete MOSFET H-bridge | `gerbers-v.663399ADS.zip` |

**Enclosure:** v0.663399u (compatible with both PCB versions)

> **Note on Versioning:** These are development versions. The project uses fractional version numbers during active development to indicate pre-release status. First production-ready release will be v1.0.

### v0.663399-T (Tri-Modal) - In Development

The "T" designates **Tri-Modal** output: haptic (motor), visual (RGB LED), and audio (amplified speaker). This is the first revision with a dedicated audio amplifier rather than a simple piezo sounder.

The PCB uses dedicated ICs instead of discrete MOSFETs:

- **DRV2603** - Texas Instruments haptic driver (replaces discrete H-bridge)
- **MAX9938** - Current sense amplifier for motor diagnostics
- **MAX98357A** - I2S audio amplifier (future audio feedback feature)
- **Dialight 587-2056-147F** - Addressable RGB LED (replaces WS2812B)

**Firmware status:** Not yet adapted for dedicated IC hardware. GPIO mappings and driver code TBD.

**Build Notes for v0.663399-T:**

**JP1 - LRA/ERM Motor Selection:**
The DRV2603 supports both LRA (Linear Resonant Actuator) and ERM (Eccentric Rotating Mass) motors via a 3-pad jumper:
- **Default (LRA):** JP1 etched between pads 1-2 (no modification needed)
- **For ERM motors:** Scratch/break the 1-2 trace, then solder blob pads 2-3

This approach avoids locking the design to one motor type or consuming a GPIO for runtime selection.

**Motor Selection Note:**
The development path uses a low-power LRA (0.8G, 54mA max) compared to the higher-powered ERM in v0.663399ADS production (15K RPM, 120mA). This is an intentional comparison of a high-power ERM against the lowest-power LRA available - not representative of all LRA options. Higher-force LRAs exist but draw more current.

**⚠️ DRV2603 LRA Resonance Compatibility:**

The DRV2603 auto-resonance tracking range is **140-235 Hz**. This is a critical constraint for LRA selection:

| LRA Size | Typical Resonance | DRV2603 Compatible |
|----------|-------------------|-------------------|
| 8mm | 200-280 Hz | ⚠️ Most are OUT OF RANGE |
| 10mm | 150-200 Hz | ✅ Generally compatible |
| 12mm+ | 120-170 Hz | ✅ Compatible |

**Design Decision:** After evaluating multiple 8mm LRAs, nearly all had resonance frequencies above 235 Hz (outside DRV2603 tracking range). Switching to 10mm LRA was chosen over the DRV2604L (wider range but significantly higher IC cost). 8mm and 10mm LRAs are similarly priced, making motor substitution the economical choice.

**Alternative:** The DRV2604L supports 45-300 Hz resonance tracking but costs significantly more. Only consider if 8mm form factor is absolutely required.

**PCB Revision Notes (December 2025):**

Recent hardware improvements to v0.663399-T:

1. **Current Sense Shunt - Kelvin Connection:** The MAX9938 current sense topology now uses proper 4-wire (Kelvin) sensing with matched-length traces from shunt to sense amplifier. This eliminates voltage drop errors from current-carrying PCB traces.

2. **DRV2603 PWM Series Resistor:** Added 22Ω series resistor on GPIO PWM output to DRV2603. Suppresses ringing from GPIO driving capacitive load. At 25kHz PWM, values up to 100Ω would work; 22Ω is conservative standard practice.

**Component Sizes:**
This revision diverges from strictly 0805 passives:
- **0603:** Several capacitors in current sense topology + battery sense filter cap
- **0402:** Shunt resistor for MAX9938 current sense

Assembly complexity increases slightly, but smaller components are localized to the current sense area.

**Optional Components:**
- **MAX9938 + shunt R:** Can be omitted entirely; solder-blob the shunt pads if skipping
- **Battery sense filter cap (0603):** Optional - current v0.663399ADS production runs without a low-pass filter cap and ADC works fine

**Motor/Speaker Connector:**
The motor connector is now 4-pin, combining motor and speaker outputs. The existing enclosure (v0.663399u) has 3 overlapping 10mm circles in the bottom designed for the motor - this accommodates a small speaker, though audio quality will be modest (adequate for tones/feedback, not music playback). Finding speakers that fit the 10mm constraint is challenging but several candidates identified.

**Battery Sense Redesign:**
The battery monitoring circuit no longer requires a dedicated enable GPIO. Instead, a self-latching voltage divider design is used - the ADC pin is driven HIGH or LOW to control the measurement. This frees up GPIO21 compared to v0.663399ADS.

**3.3V Addressable RGB:**
The Dialight 587-2056-147F was specifically chosen because it is rated for 3.3V operation, unlike the WS2812B which is nominally 5V (and required level shifting or tolerance of out-of-spec operation).

**GPIO Utilization:**
This revision uses **all available GPIO** broken out on the Seeed XIAO ESP32-C6. No spare pins remain for future expansion on this form factor.

**Board Size:**
The PCB is slightly larger near the MCU module area to accommodate a continuous ground strip across all board edges, improving EMI performance and ground return paths.

### v0.663399ADS (MOSFET H-bridge) - Production Ready

The current production hardware uses discrete MOSFET H-bridge topology. This is the version to build if you want working hardware today.

**Archive:** The complete MOSFET H-bridge design is preserved in `pcb/MLE_HAPTICS_PULSER_MOSFET_H_BRIDGE.7z`

## Hardware/Firmware Compatibility

### v0.663399ADS (MOSFET H-bridge) - ✅ Fully Compatible

Firmware is fully updated for v0.663399ADS hardware. GPIO crosstalk fixes are implemented:
- H-bridge IN1 (forward) on GPIO18 (moved from GPIO20)
- H-bridge IN2 (reverse) on GPIO19
- Button directly connected to GPIO1 (no jumper wire required)

```c
// Current GPIO definitions (v0.663399ADS)
#define GPIO_BUTTON      1  // Direct connection
#define GPIO_M_IN2      19  // H-bridge reverse
#define GPIO_M_IN1      18  // H-bridge forward
```

### v0.663399-T (Dedicated IC) - ⏳ Firmware Pending

The dedicated IC hardware uses different components requiring new firmware:
- DRV2603 haptic driver (I2C or analog control - TBD)
- MAX98357A audio amp (I2S interface)
- Dialight addressable RGB (different protocol than WS2812B)
- MAX9938 current sense (analog input)

GPIO mapping for v0.663399-T will be documented once firmware development begins.

## Repository Structure

```
hardware/
├── pcb/                                    # KiCad PCB project
│   ├── MLE_HAPTICS_PULSER.kicad_pro       # KiCad project file
│   ├── MLE_HAPTICS_PULSER.kicad_sch       # Schematic (v0.663399-T dedicated IC)
│   ├── MLE_HAPTICS_PULSER.kicad_pcb       # PCB layout (v0.663399-T dedicated IC)
│   ├── MLE_HAPTICS_PULSER_MOSFET_H_BRIDGE.7z  # Archive of v0.663399ADS design
│   ├── libraries/                          # Custom KiCad libraries
│   │   ├── mlehaptics_library/            # Project symbols and footprints
│   │   └── 3dmodels/                      # 3D models for components
│   ├── production/
│   │   ├── gerbers/
│   │   │   ├── gerbers-v.663399-T.zip     # v0.663399-T (dedicated IC) - IN DEVELOPMENT
│   │   │   └── gerbers-v.663399ADS.zip    # v0.663399ADS (MOSFET) - PRODUCTION
│   │   └── schematic/
│   │       ├── MLE_HAPTICS_PULSER_663399-T.pdf              # Dedicated IC schematic
│   │       └── MLE_HAPTICS_PULSER_MOSFET_H_BRIDGE_663399ADS.pdf  # MOSFET schematic
│   └── images/                             # PCB visualizations
│       ├── pcb_top_view.png
│       └── pcb_bottom_view.png
│
├── enclosure/                              # Mechanical design
│   └── phase1/                             # Phase 1 case design
│       ├── MLE_HAPTICS_PULSER-v0.663399u.FCStd  # FreeCAD source file
│       ├── stl/                            # STL files for 3D printing
│       │   ├── MLE_HAPTICS_PULSER-v0.663399u-bodyTop.stl
│       │   └── MLE_HAPTICS_PULSER-v0.663399u-bodyBottom.stl
│       ├── step/                           # STEP files for CAD interop
│       │   ├── MLE_HAPTICS_PULSER-v0.663399u-bodyTop.step
│       │   ├── MLE_HAPTICS_PULSER-v0.663399u-bodyBottom.step
│       │   └── MLE_HAPTICS_PULSER-v0.663399u-bodyTop_CLRMOD.step
│       └── images/                         # Enclosure renders
│           ├── MLE_HAPTICS_PULSER-v0.663399u.png
│           └── MLE_HAPTICS_PULSER-v0.663399u_WITH_PCB.png
│
├── datasheets/                             # Component datasheets
│   ├── esp32-c6_datasheet_en.pdf          # MCU
│   ├── XIAO-ESP32-C6_v1.0_SCH_PDF_24028.pdf  # Dev board schematic
│   ├── WS2812B.pdf                         # RGB LED (v0.663399ADS)
│   ├── drv2603.pdf                         # Haptic driver IC (v0.663399-T)
│   ├── max9938.pdf                         # Current sense amp (v0.663399-T)
│   ├── max98357a-max98357b.pdf             # Audio amp (v0.663399-T)
│   ├── Dialight_datasheet_587-2056-147F_Addressable_RGB.pdf  # RGB LED (v0.663399-T)
│   ├── JYLRA0825Z.pdf                      # ERM motor option
│   └── PYU-RL_GROUP_521_ROHS_L.pdf         # ERM motor option
│
└── docs/                                   # KiCad library source files
    ├── DRV2603RUNR.zip                     # DRV2603 KiCad library
    ├── MAX9938TEUK_T.zip                   # MAX9938 KiCad library
    ├── MAX98357AETE_T.zip                  # MAX98357A KiCad library
    ├── LIB_587-2056-147F.zip               # Dialight RGB KiCad library
    └── OPL_Kicad_Library.zip               # Open Parts Library
```

## Quick Start for Builders

### Choose Your Version

**Building today? Use v0.663399ADS** (MOSFET H-bridge)
- Firmware ready, fully tested
- Production gerbers: `gerbers-v.663399ADS.zip`
- Schematic: `MLE_HAPTICS_PULSER_MOSFET_H_BRIDGE_663399ADS.pdf`

**Experimenting with new ICs? Use v0.663399-T** (Dedicated IC)
- Hardware ready, firmware pending
- Development gerbers: `gerbers-v.663399-T.zip`
- Schematic: `MLE_HAPTICS_PULSER_663399-T.pdf`

### PCB Manufacturing

**For production builds (recommended):**
1. **Download gerbers:** `pcb/production/gerbers/gerbers-v.663399ADS.zip` (MOSFET H-bridge)
2. **Upload to fab house:** JLCPCB, PCBWay, OSH Park, etc.
3. **Recommended specs:**
   - 2-layer PCB
   - 1.6mm thickness
   - HASL or ENIG finish
   - Any color (black recommended for aesthetics)

**For development builds (dedicated IC - firmware not ready):**
1. **Download gerbers:** `pcb/production/gerbers/gerbers-v.663399-T.zip`
2. **Note:** Firmware support for DRV2603 not yet implemented

### Component Sourcing

**Bill of Materials (BOM):** See main repository `/docs/` for complete parts list

### Battery Specification

The enclosure is designed for two EEMB LP402535 LiPo batteries wired in parallel (1S2P configuration).

**Reference Battery:** [EEMB LP402535 320mAh 3.7V](https://www.amazon.com/dp/B08HD1N273)

| Specification | Value |
|---------------|-------|
| Model | LP402535 (4.0mm × 25mm × 35mm naming convention) |
| Voltage | 3.7V nominal |
| Capacity | 320mAh typical (300mAh minimum) |
| **Dimensions** | **25.5 × 36 × 4.3mm** (W × L × H) |
| Weight | ~6g per cell |
| Connector | Molex-style 2-pin (⚠️ verify polarity!) |
| Protection | PCM with overcharge/overdischarge/overcurrent/short circuit |
| Certifications | UN 38.3, IEC, UL |

**Configuration:** Two cells in parallel (1S2P)
- Combined capacity: 640mAh
- Voltage: 3.7V (unchanged - parallel connection)
- Fits in enclosure battery compartment

**Substitution Guidelines:**

If sourcing alternative batteries, match these critical dimensions:
- **Thickness:** ≤4.5mm (enclosure clearance)
- **Width:** ~25mm (battery slot width)
- **Length:** ~35mm (battery slot length)

Batteries with similar "402535" or "402530" designations should fit. Always verify polarity before connecting - LiPo connector polarity is NOT standardized.

**Key Components (v0.663399ADS - MOSFET H-bridge):**
- Seeed XIAO ESP32-C6 development board
- ERM vibration motors (φ10mm × 3mm)
- WS2812B RGB LEDs (optional - for therapy light feature)
- H-bridge MOSFETs (AO3400A/AO3401A family)
- Dual EEMB LP402535 320mAh LiPo batteries (640mAh combined)
- Passive components (resistors, capacitors)

**Key Components (v0.663399-T - Dedicated IC):**
- Seeed XIAO ESP32-C6 development board
- **10mm LRA motor** (resonance 150-200 Hz for DRV2603 compatibility - see note above)
- **E-Switch TL1105 (65gf)** - Soft-touch tactile switch (see note below)
- DRV2603 haptic driver IC (Texas Instruments)
- MAX9938 current sense amplifier (Analog Devices)
- MAX98357A I2S audio amplifier (Analog Devices)
- Dialight 587-2056-147F addressable RGB LED
- Dual EEMB LP402535 320mAh LiPo batteries (640mAh combined)
- Passive components (resistors, capacitors, 22Ω series R for PWM)

**Button Selection Note:**
The E-Switch TL1105 with 65gf actuation force was chosen over standard SMT 6×6×5mm tact switches (typically 160-260gf) for user comfort during therapy sessions. The soft-touch feel reduces finger fatigue and provides a gentler, less jarring interaction appropriate for therapeutic use. The metal dome mechanism produces a subtle tactile "tick" rather than a loud click. Higher BOM cost accepted for improved user experience.

### 3D Printing the Enclosure

**Print Settings:**
- **Layer height:** 0.2mm
- **Infill:** 20% (or higher for durability)
- **Material:** See material guide below

**Files to Print:**
- `enclosure/phase1/stl/MLE_HAPTICS_PULSER-v0.663399u-bodyTop.stl` (Standard)
- `enclosure/phase1/stl/MLE_HAPTICS_PULSER-v0.663399u-bodyBottom.stl`

**STEP Files:** Available in `enclosure/phase1/step/` for CAD modification

### Enclosure Material Selection

The therapy light feature (GPIO17 WS2812B LED) requires case materials with light transmission capability. See main repository documentation for details.

**Material Options:**
- **Light-blocking materials** (motor-only builds): Black nylon SLS, dark PLA/ABS, carbon fiber
- **Light-transmitting materials** (therapy light builds): Clear resin, translucent PETG, light-colored SLS nylon
- **Test before committing:** Print a test piece of your chosen material/color to verify light transmission

### Enclosure Variants: Standard vs CLRMOD

**Standard bodyTop (Default):**

File: `MLE_HAPTICS_PULSER-v0.663399u-bodyTop.step`

Includes access features for development and visual feedback:
- **Reset/Boot pin pinholes:** Access to Seeed XIAO ESP32-C6 Reset and Boot pins for programming
- **LED light transmission holes:** Allows visibility of:
  - **Red battery charge LED:** Hardware-controlled charge status indicator (not firmware accessible)
  - **Amber GPIO15 user LED:** On-board status LED (firmware-controlled via GPIO15)

**Use Standard bodyTop when:**
- Need Reset/Boot pin access for development, debugging, or frequent firmware updates
- Want visual battery charging status indication (red LED)
- Want GPIO15 status LED visible through case for debugging
- Building prototypes or development units

---

**CLRMOD bodyTop (Clean Model):**

File: `MLE_HAPTICS_PULSER-v0.663399u-bodyTop_CLRMOD.step`

Simplified variant that removes access holes for clean, diffused light transmission:
- **No Reset/Boot pin access:** Pinholes removed (cleaner appearance, no programming access)
- **No indicator LED holes:** Prevents focused LED hotspots through case:
  - Red battery charge status LED (hardware-controlled) - visible as diffused glow through translucent material
  - Amber GPIO15 user LED (firmware status indicator) - visible as diffused glow through translucent material
  - **Result with clear/translucent materials:** Clean, uniform illumination without bright hotspots

**Use CLRMOD bodyTop when:**
- **Printing with clear SLA resin or translucent materials** - provides diffused LED visibility without focused hotspots
- Building production/end-user devices where Reset/Boot access not needed
- Want WS2812B therapy light to illuminate entire case uniformly
- Prioritizing clean aesthetics over direct indicator LED visibility
- Device will be programmed and tested before final case assembly
- Creating a professional, finished product with diffused lighting effect

**Note:** CLRMOD is only available as STEP file - import into your CAD software and export to STL if needed.

## Hardware Features

### PCB Specifications
- **MCU:** Seeed XIAO ESP32-C6 (RISC-V @ 160MHz)
- **Motor control:** Discrete MOSFET H-bridge (TB6612FNG-style topology)
- **Status LED:** On-board LED (GPIO15, amber)
- **Charge LED:** Hardware battery charge indicator (red, not firmware-controlled)
- **Therapy light:** WS2812B RGB LED (GPIO17, optional)
- **Battery monitoring:** ADC-based voltage measurement
- **Power management:** Deep sleep with button wake capability
- **Connectivity:** BLE 5.0 GATT server

### Current GPIO Pin Mapping (v0.663399ADS)

```
GPIO0:  Back-EMF sensing (ADC1_CH0, OUTA from H-bridge)
GPIO1:  Button input (direct connection, hardware debounced with 10k pull-up)
GPIO2:  Battery voltage monitor (ADC1_CH2, resistor divider)
GPIO15: Status LED (on-board amber LED, ACTIVE LOW, firmware-controlled)
GPIO16: Therapy light enable (P-MOSFET, ACTIVE LOW)
GPIO17: Therapy light output (WS2812B DIN or simple LED)
GPIO18: H-bridge IN1 (motor forward control) ← MOVED FROM GPIO20
GPIO19: H-bridge IN2 (motor reverse control) - UNCHANGED
GPIO21: Battery monitor enable (P-MOSFET gate control)

Hardware LEDs (not GPIO-controlled):
- Red LED: Battery charging status (hardware-controlled by charge IC)
- Amber LED: Connected to GPIO15 (firmware-controlled user status indicator)
```

**Key Change from Previous Hardware:**
- ✅ **GPIO20 → GPIO18** for H-bridge IN1 forward (fixes ESP32-C6 GPIO19/GPIO20 crosstalk)
- ✅ **Button on GPIO1** directly (no jumper wire required)

### Enclosure Features
- **Form factor:** Designed for Seeed XIAO ESP32-C6
- **Battery compartment:** Fits dual 320mAh LiPo batteries (640mAh)
- **Button access:** Hardware button accessible through case
- **Material variants:** Supports both opaque and translucent case builds
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
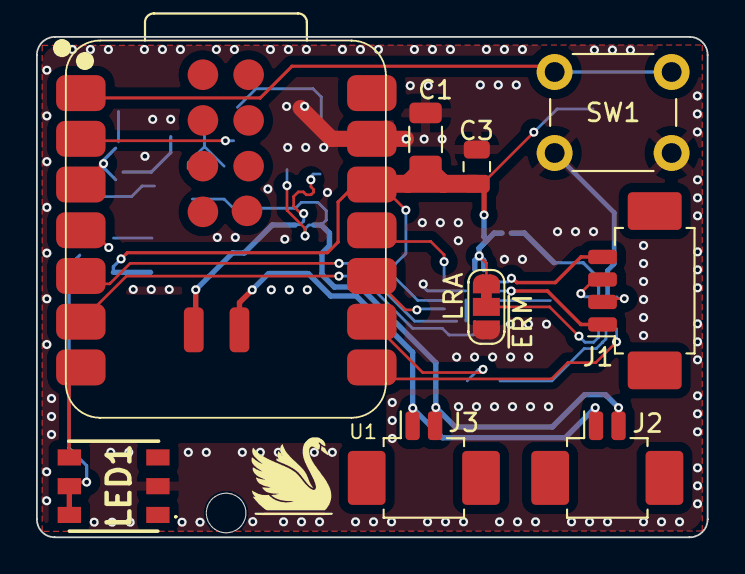
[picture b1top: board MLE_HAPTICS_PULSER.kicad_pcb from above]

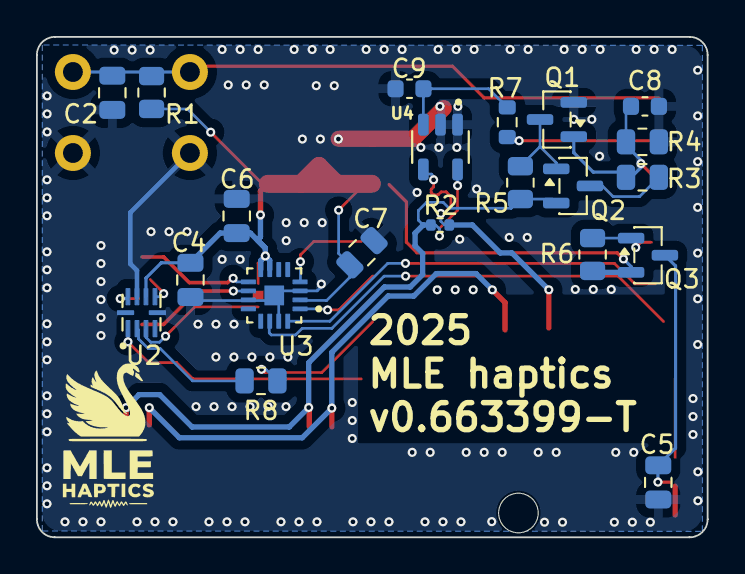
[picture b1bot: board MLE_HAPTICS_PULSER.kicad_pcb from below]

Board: 2 copper layers, 37.3 x 27.8 mm, 32 parts (22 on the bottom side), 26 nets.

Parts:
C1: 47uF; C_1206_3216Metric
C2: 1uF; C_0805_2012Metric
C3, C6: 10uF; C_0805_2012Metric
C4, C5, C7: 0.1uF; C_0805_2012Metric
C8, C9: 0.1uF; C_0603_1608Metric
G1: mlehaptics_art; mlehaptics_pcb_art
H1: MountingHole; MountingHole_2.2mm_M2_DIN965
J1: Conn_01x04_MountingPin; Molex_PicoBlade_53261-0471_1x04-1MP_P1.25mm_Horizontal
J2, J3: Conn_01x02_MountingPin; Molex_PicoBlade_53261-0271_1x02-1MP_P1.25mm_Horizontal
JP1: LRA/~{ERM} Select; SolderJumper-3_P1.3mm_Bridged12_RoundedPad1.0x1.5mm_NumberL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
LED1: 587-2056-147F; Dialight 587-2056-147F Addressable RGB
Q1: DMN2004K-7; SOT-23
Q2, Q3: DMP2004K-7; SOT-23
R1, R4: 10K; R_0805_2012Metric
R2: 100m; R_0402_1005Metric
R3: 3.3K; R_0805_2012Metric
R5, R6: 100K; R_0805_2012Metric
R7: 10K; R_0603_1608Metric
R8: 22; R_0805_2012Metric
SW1: SW_Push; SW_PUSH_6mm_H5mm
U1: XIAO-ESP32-C6-SMD; XIAO-ESP32C6-SMD
U2: DRV2603RUNR; DRV2603
U3: MAX98357AETE_T; QFN50P300X300X80-17N
U4: MAX9938TEUK_T; SOT95P280X145-5N

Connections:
3V3: C1.2, C3.2, C4.1, C6.2, C7.2, JP1.1 (A), Q3.2 (S), R1.1, R6.2, U1.12 (3V3), U2.7 (VDD), U3.2 (GAIN_SLOT), U3.7 (VDD), U3.8 (VDD__1)
+BATT: J2.2, J3.2, Q2.2 (S), R2.1, R5.2, U4.5 (RS+)
-BATT: J2.1, J3.1, U1.16 (GND)
/ERM/~LRA: JP1.2 (C), U2.3 (LRA/~ERM)
/VBAT+LOAD: R2.2, U1.15 (BAT), U4.4 (RS-)
/WS2812B_VDD_ENABLE: Q3.1 (G), R6.1, U1.4 (GPIO21_D3)
/WS2812_VDD: C5.1, LED1.5 (VDD_1), LED1.6 (VDD_2), Q3.3 (D)
/drv2603_en: U1.8 (GPIO17_D7_RX), U2.1 (EN)
/drv2603_pwm: R8.1, U1.9 (GPIO19_D8_SCK)
/led_ctr: LED1.4 (DI), U1.7 (GPIO16_D6_TX)
/max9938t_out: R7.2, U1.2 (GPIO1_A1_D1)
/max_bit_clock: U1.5 (GPIO22_D4_SDA), U3.16 (BCLK)
/max_data_input: U1.10 (GPIO20_D9_MISO), U3.1 (DIN)
/max_frame_clock: U1.6 (GPIO23_D5_SCL), U3.14 (LRCLK)
/max_out_N: J1.1, U3.10 (OUTN)
/max_out_P: J1.4, U3.9 (OUTP)
/max_sd_mode: U1.11 (GPIO18_D10_MOSI), U3.4 (SD_MODE)
/motor_out_N: J1.3, U2.6 (OUT_M)
/motor_out_P: J1.2, U2.9 (OUT_P)
/readBatt: C8.1, Q1.1 (G), R3.1, R4.2, U1.3 (GPIO2_A2_D2)
/sw1: C2.1, R1.2, SW1.1, U1.1 (GPIO0_A0_D0)
GND: C1.1, C2.2, C3.1, C4.2, C5.2, C6.1, C7.1, C8.2, C9.2, JP1.3 (B), LED1.2 (GND), Q1.2 (S), R4.1, SW1.2, U1.13 (GND), U2.5 (GND), U2.8 (GND__1), U2.10 (GND__2), U3.3 (GND), U3.11 (GND__1), U3.15 (GND__2), U3.17 (EP), U4.1 (GND), U4.2 (GND__1)
unnamed: Q1.3 (D), Q2.1 (G), R5.1
unnamed: Q2.3 (D), R3.2
unnamed: R8.2, U2.2 (PWM)
unnamed: C9.1, R7.1, U4.3 (OUT)

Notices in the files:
hardware/README.md:
Hardware licensed under **CERN Open Hardware Licence Version 2 - Strongly Reciprocal (CERN-OHL-S v2)
This is a copyleft license for hardware designs. Any modifications or derivative works must be released under the same license terms.
Full license text: [CERN-OHL-S-2.0](https://ohwr.org/cern_ohl_s_v2.txt)
